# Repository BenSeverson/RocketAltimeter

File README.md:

High Power Rocket Altimeter
===============
This is an altimeter for [high power rocketry](https://en.wikipedia.org/wiki/High-power_rocketry). Sources include the PIC Micro firmware, Eagle PCB layout, and Windows configuration/log download program.

Features:
- dual payload deployment
- altitude and deployment logging to non-volatile EEPROM
- native USB support for configuration and log downloading
- audible max altitude readout
- pre-launch readiness audible indicator and rocket recovery/location beep
- simple 2-layer PCB with mainly SMT components designed to be made at home

**Note:** I started this project back in 2007 when I was in college but life got in the way before I had a chance to complete it. I've uploaded it here for archival purposes and maybe someone will find it useful. If you are looking for an open source altimeter, I'd highly suggest [Altus Metrum](http://altusmetrum.org/) which is complete, much more advanced, and actually being developed/maintained.

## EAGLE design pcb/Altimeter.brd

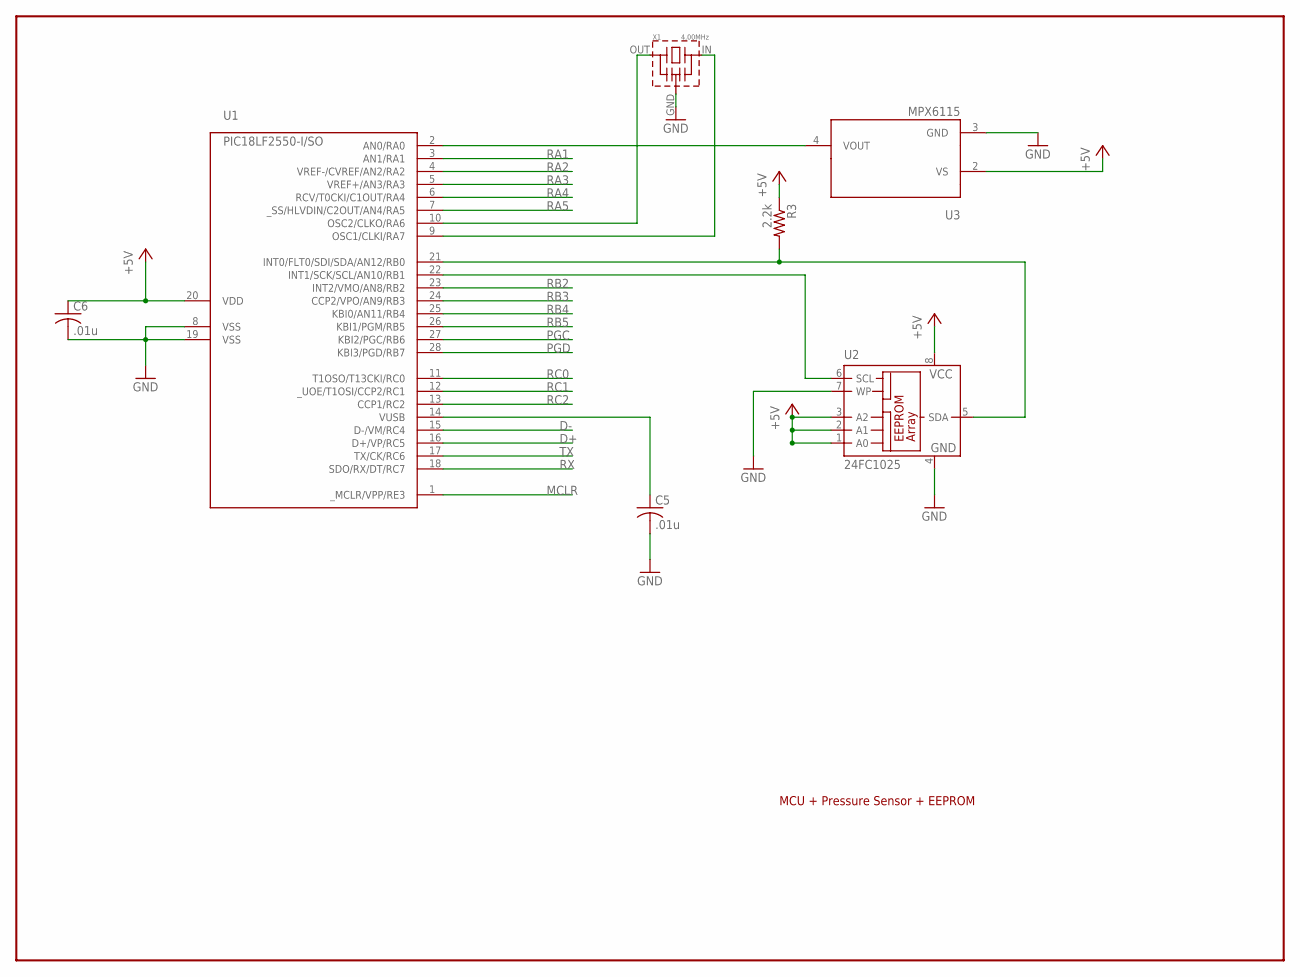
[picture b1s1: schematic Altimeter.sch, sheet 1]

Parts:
C5, C6: .01u; C1206
R3: 2.2k; R1206
U1: PIC18LF2550-I/SO; SO-28W
U2: 24FC1025; SO-08M
U3: MPX6115; SSOP8
X1: 4.00MHz; 7434

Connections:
+5V: C6.1, R3.1, U1.20 (VDD), U2.1 (A0), U2.2 (A1), U2.3 (A2), U2.8 (VCC), U3.2 (VS); also elsewhere on the board
D+: U1.16 (D+/VP/RC5); also elsewhere on the board
D-: U1.15 (D-/VM/RC4); also elsewhere on the board
GND: C5.2, C6.2, U1.8 (VSS), U1.19 (VSS), U2.4 (GND), U2.7 (WP), U3.3 (GND), X1.GND (VSS); also elsewhere on the board
MCLR: U1.1 (_MCLR/VPP/RE3); also elsewhere on the board
unnamed: U1.2 (AN0/RA0), U3.4 (VOUT)
unnamed: U1.22 (INT1/SCK/SCL/AN10/RB1), U2.6 (SCL)
unnamed: R3.2, U1.21 (INT0/FLT0/SDI/SDA/AN12/RB0), U2.5 (SDA)
unnamed: U1.10 (OSC2/CLKO/RA6), X1.OUT (1)
unnamed: U1.9 (OSC1/CLKI/RA7), X1.IN (3)
unnamed: C5.1, U1.14 (VUSB)
PGC: U1.27 (KBI2/PGC/RB6); also elsewhere on the board
PGD: U1.28 (KBI3/PGD/RB7); also elsewhere on the board
RA1: U1.3 (AN1/RA1)
RA2: U1.4 (VREF-/CVREF/AN2/RA2)
RA3: U1.5 (VREF+/AN3/RA3); also elsewhere on the board
RA4: U1.6 (RCV/T0CKI/C1OUT/RA4); also elsewhere on the board
RA5: U1.7 (_SS/HLVDIN/C2OUT/AN4/RA5)
RB2: U1.23 (INT2/VMO/AN8/RB2); also elsewhere on the board
RB3: U1.24 (CCP2/VPO/AN9/RB3); also elsewhere on the board
RB4: U1.25 (KBI0/AN11/RB4)
RB5: U1.26 (KBI1/PGM/RB5)
RC0: U1.11 (T1OSO/T13CKI/RC0); also elsewhere on the board
RC1: U1.12 (_UOE/T1OSI/CCP2/RC1); also elsewhere on the board
RC2: U1.13 (CCP1/RC2); also elsewhere on the board
RX: U1.18 (SDO/RX/DT/RC7); also elsewhere on the board
TX: U1.17 (TX/CK/RC6); also elsewhere on the board

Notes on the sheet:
MCU + Pressure Sensor + EEPROM

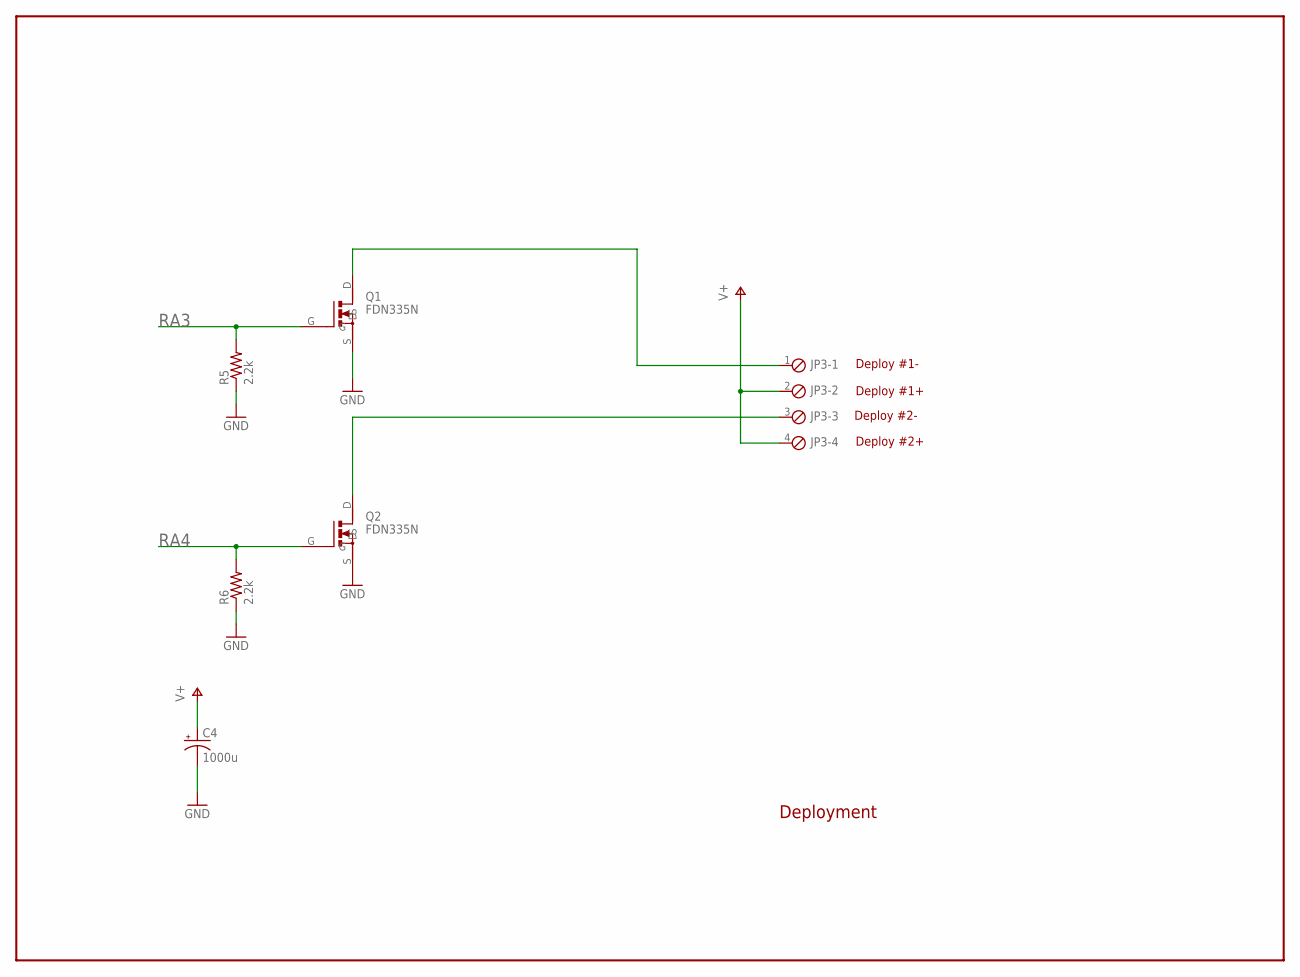
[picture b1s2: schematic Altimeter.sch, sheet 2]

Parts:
C4: 1000u; PANASONIC_G
JP3: MPT4; 4POL254
Q1, Q2: FDN335N; SSOT3
R5, R6: 2.2k; R1206

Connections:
GND: C4.-, Q1.S, Q2.S, R5.1, R6.1; also elsewhere on the board
unnamed: JP3.1, Q1.D
unnamed: JP3.3, Q2.D
RA3: Q1.G, R5.2; also elsewhere on the board
RA4: Q2.G, R6.2; also elsewhere on the board
V+: C4.+, JP3.2, JP3.4; also elsewhere on the board

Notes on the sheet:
Deployment
Deploy #1-
Deploy #1+
Deploy #2+
Deploy #2-

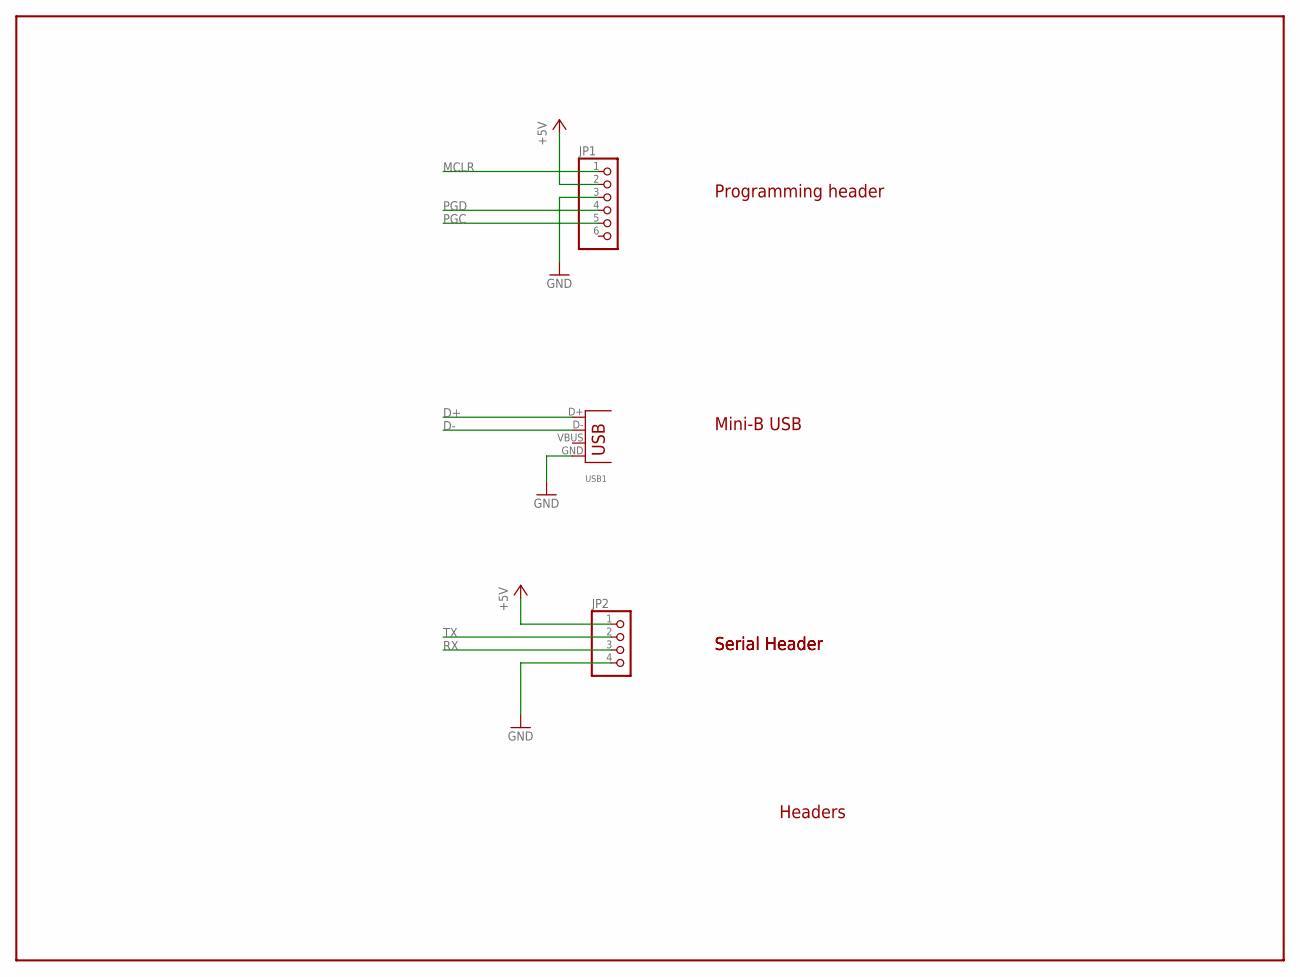
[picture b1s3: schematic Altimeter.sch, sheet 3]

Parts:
JP1: PINHD-1X6; 1X06
JP2: PINHD-1X4; 1X04
USB1: USB-MB-S

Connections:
+5V: JP1.2, JP2.1; also elsewhere on the board
D+: USB1.D+; also elsewhere on the board
D-: USB1.D-; also elsewhere on the board
GND: JP1.3, JP2.4, USB1.GND; also elsewhere on the board
MCLR: JP1.1; also elsewhere on the board
PGC: JP1.5; also elsewhere on the board
PGD: JP1.4; also elsewhere on the board
RX: JP2.3; also elsewhere on the board
TX: JP2.2; also elsewhere on the board

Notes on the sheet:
Programming header
Mini-B USB
Serial Header
Headers

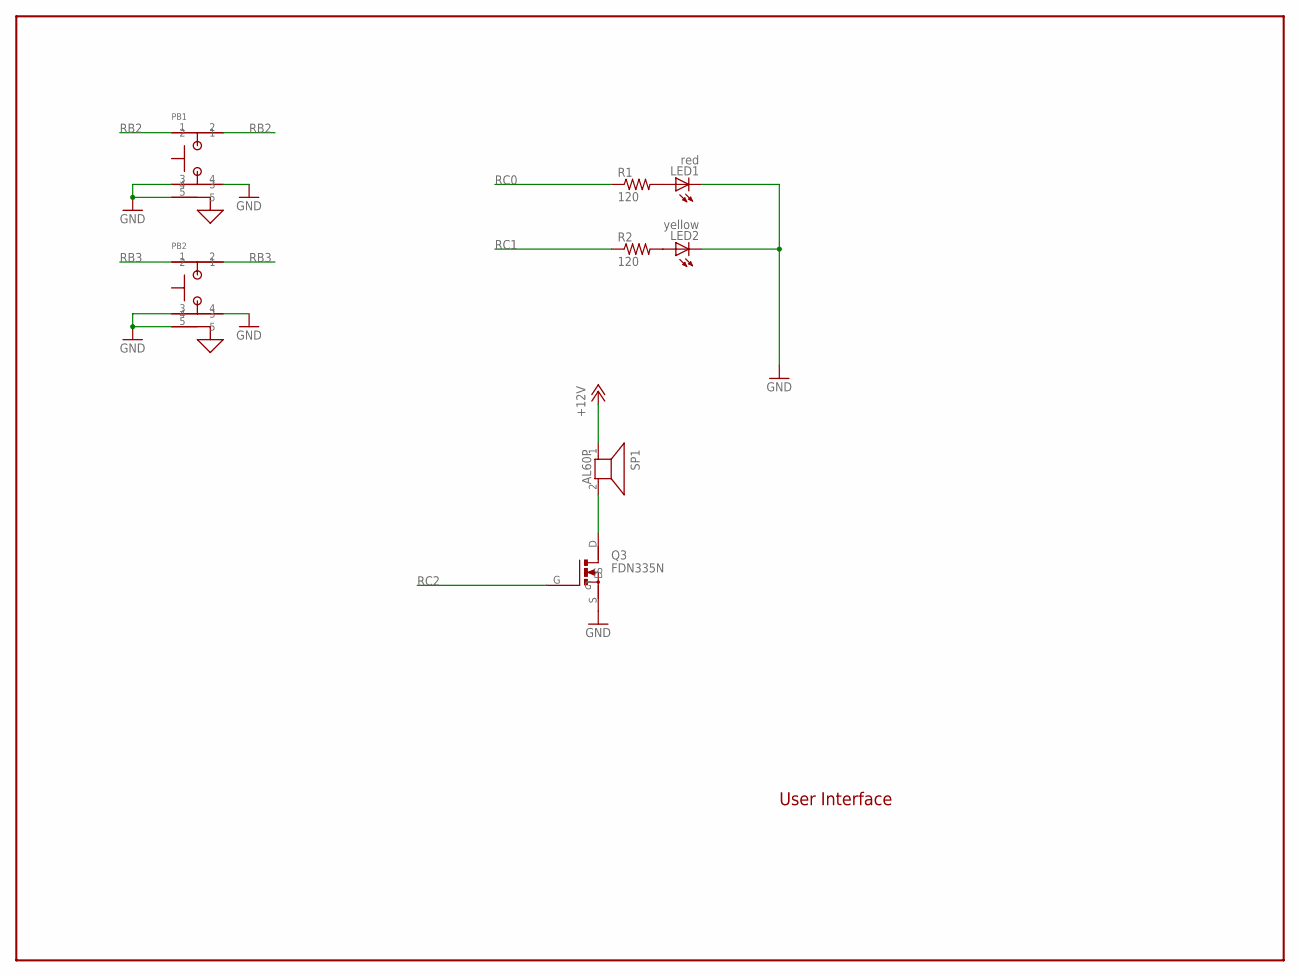
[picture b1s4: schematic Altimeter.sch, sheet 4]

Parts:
LED1: red; 1206
LED2: yellow; 1206
PB1, PB2: ALPS_SWITCH_SMD; ALPS-SMD-TACT
Q3: FDN335N; SSOT3
R1, R2: 120; R1206
SP1: AL60P; KB-BUZZER

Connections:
+12V: SP1.1; also elsewhere on the board
GND: LED1.C, LED2.C, PB1.3, PB1.4, PB1.5, PB2.3, PB2.4, PB2.5, Q3.S; also elsewhere on the board
unnamed: LED1.A, R1.2
unnamed: LED2.A, R2.2
unnamed: Q3.D, SP1.2
RB2: PB1.1, PB1.2; also elsewhere on the board
RB3: PB2.1, PB2.2; also elsewhere on the board
RC0: R1.1; also elsewhere on the board
RC1: R2.1; also elsewhere on the board
RC2: Q3.G; also elsewhere on the board

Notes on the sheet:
User Interface

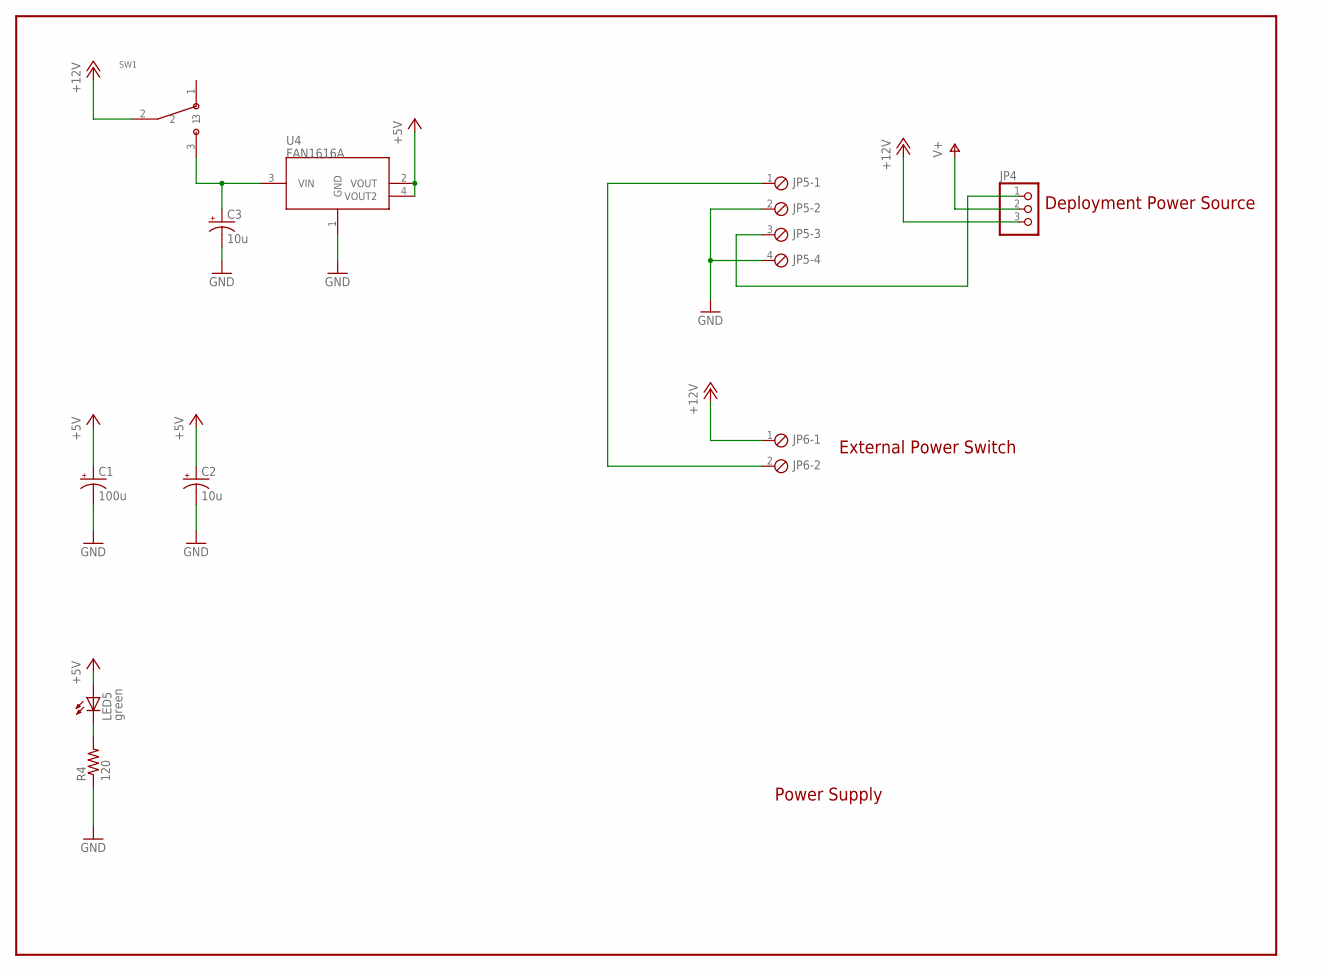
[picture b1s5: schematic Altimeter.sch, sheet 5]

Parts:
C1: 100u; PANASONIC_D
C2, C3: 10u; PANASONIC_C
JP4: PINHD-1X3; 1X03
JP5: MPT4; 4POL254
JP6: MPT2; 2POL254
LED5: green; 1206
R4: 120; R1206
SW1: EG1218; EG-SWITCH
U4: FAN1616A; SOT223

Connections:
+5V: C1.+, C2.+, LED5.A, U4.2 (VOUT), U4.4 (VOUT2); also elsewhere on the board
+12V: JP4.3, JP6.1, SW1.2; also elsewhere on the board
GND: C1.-, C2.-, C3.-, JP5.2, JP5.4, R4.1, U4.1 (GND); also elsewhere on the board
unnamed: C3.+, SW1.3, U4.3 (VIN)
unnamed: JP5.1, JP6.2
unnamed: JP4.1, JP5.3
unnamed: LED5.C, R4.2
V+: JP4.2; also elsewhere on the board

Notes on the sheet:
External Power Switch
Deployment Power Source
Power Supply

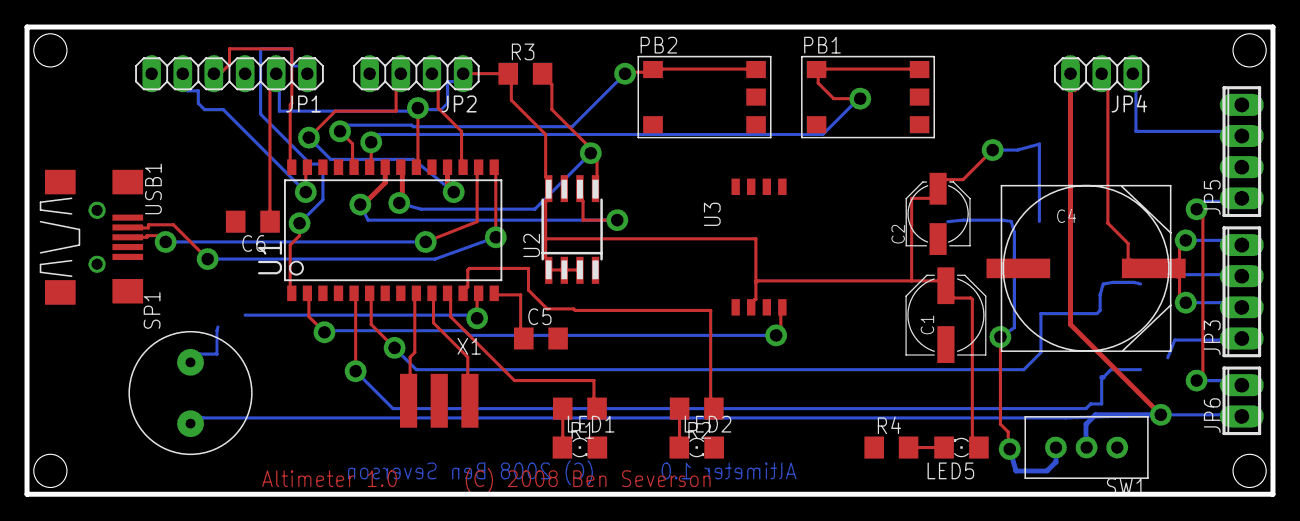
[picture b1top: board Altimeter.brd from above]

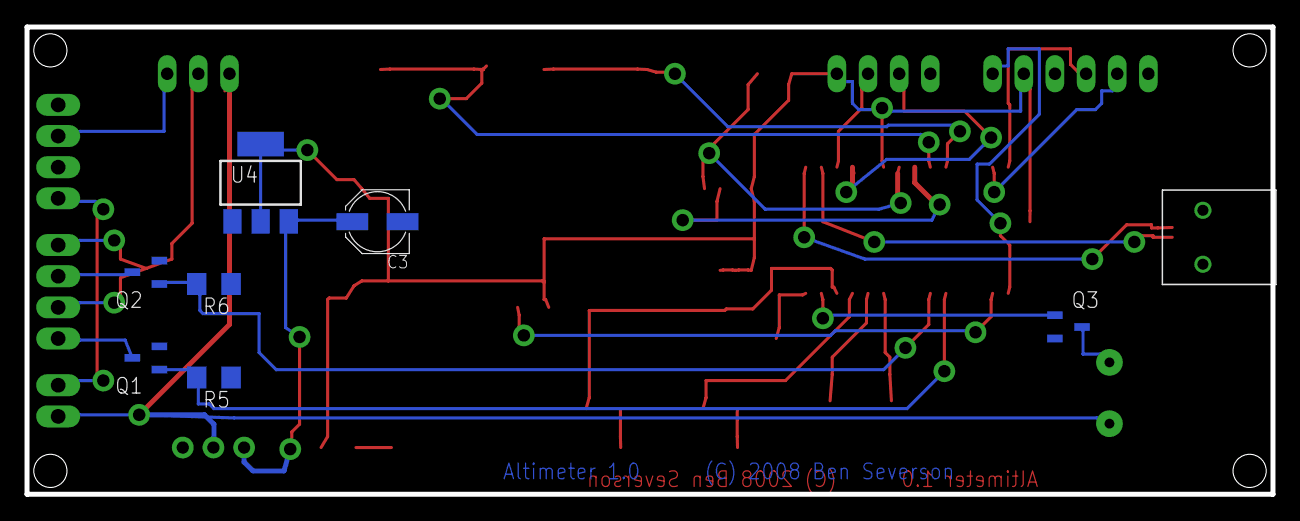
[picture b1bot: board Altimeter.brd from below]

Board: 2 copper layers, 101.6 x 38.1 mm, 34 parts (7 on the bottom side), 33 nets.

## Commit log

2008-11-30 Initial structure.
2008-12-18 Add initial version
2008-12-18 Added backup version with eeprom reading only
2008-12-18 Added pcb lib files for safe keeping
2008-12-18 added old adc reading code backup
2008-12-18 Adding initial version of altimeter firmware
2008-12-18 adding some old backup usb/i2c code
2008-12-31 * added timer to connect to altimeter * test code to display altitudes
2010-01-27 adding datasheets
2010-01-27 checking in wrt54g
2010-01-27 adding CHDK stuff
2014-10-08 move altimeter code to root
2014-10-26 initial port from SVN and removal of unrelated files
2015-08-10 upgrading project to VS2015

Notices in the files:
pcb/Altimeter.brd:
Altimeter 1.0 (C) 2008 Ben Severson
